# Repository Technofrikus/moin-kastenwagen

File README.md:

# Moinboards Kastenwagen Alu PCB

Kastenwagen Alu is based on the [Kastenwagen 1840 by NoPunin10did](https://github.com/nopunin10did/kastenwagen/tree/main). It is a 40% keyboard with a mini-numpad and dedicated arrows. The main alpha block is 13.75u long, allowing for more dedicated punctuation keys (or non-English letters) to be paired with common Minivan-like mod keys.

- Keyboard Maintainer: [Technofrikus](https://github.com/Technofrikus) from [Moinboards](https://moinboards.de)
- Onboard STM32 MCU
- Based on the original PCB by NoPunin10did, but basically completely new and NOT compatible with the previous (printed) Kastenwagen case or PCB.
- Works with VIAL

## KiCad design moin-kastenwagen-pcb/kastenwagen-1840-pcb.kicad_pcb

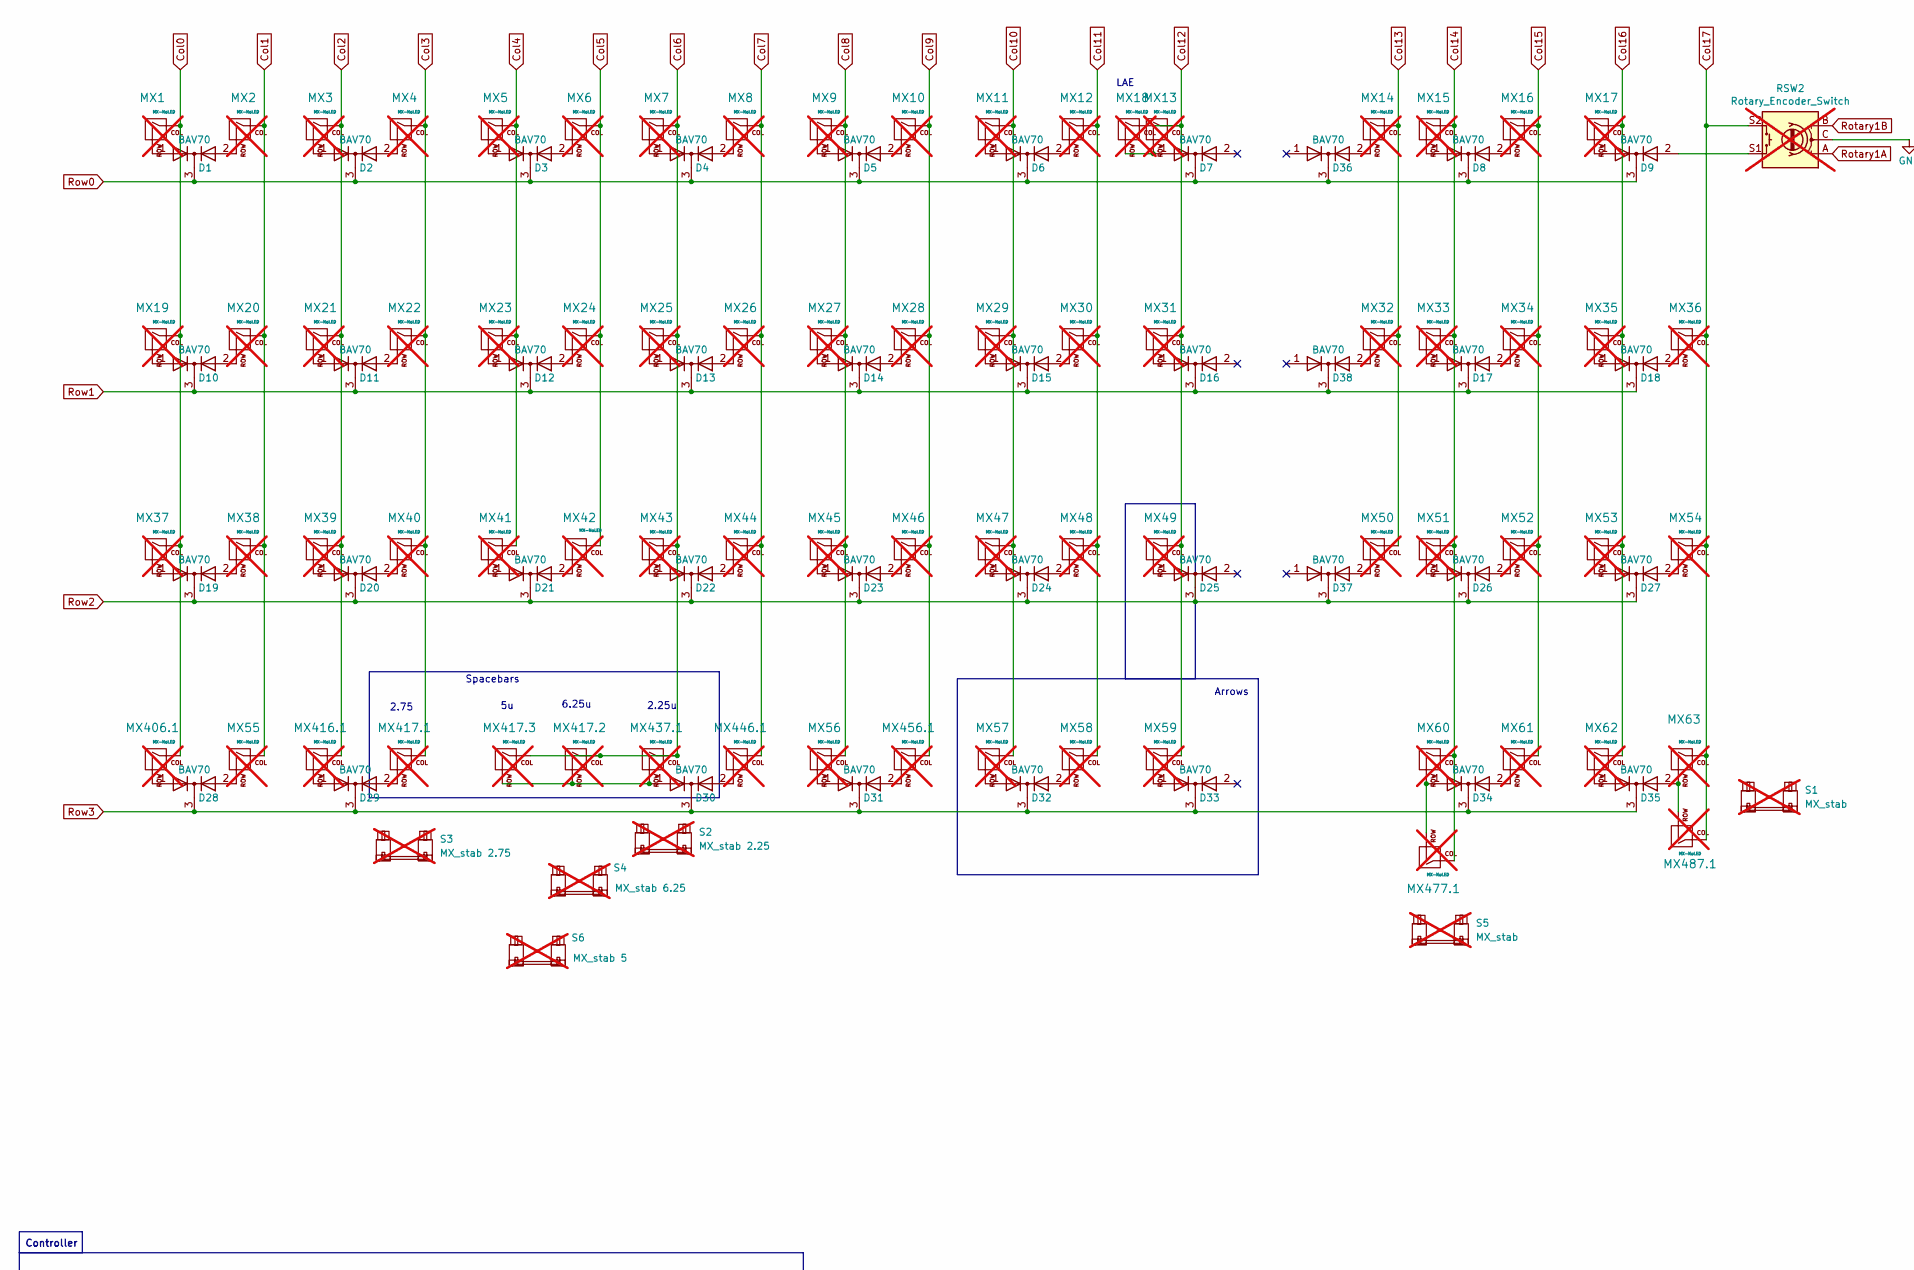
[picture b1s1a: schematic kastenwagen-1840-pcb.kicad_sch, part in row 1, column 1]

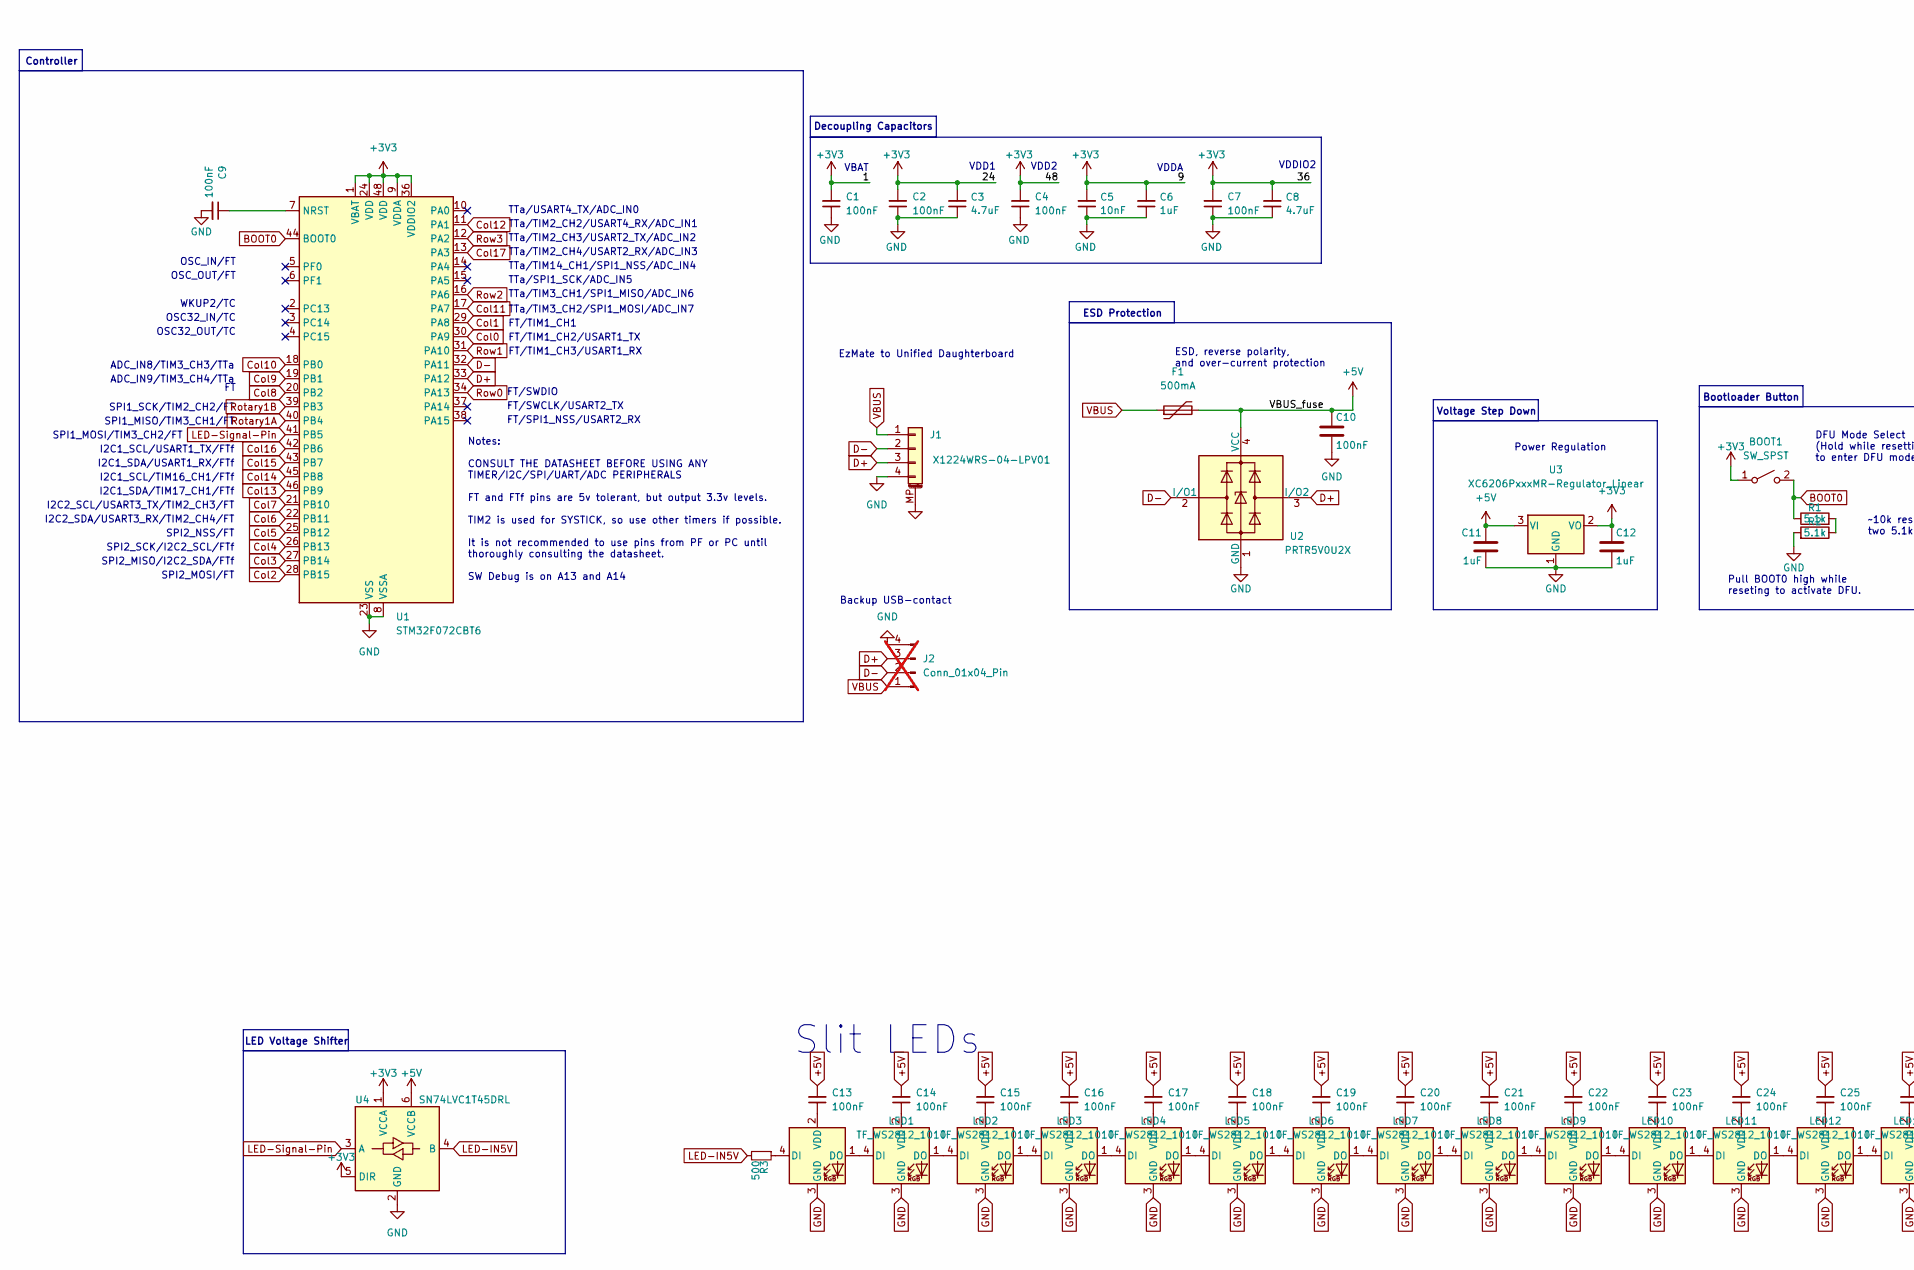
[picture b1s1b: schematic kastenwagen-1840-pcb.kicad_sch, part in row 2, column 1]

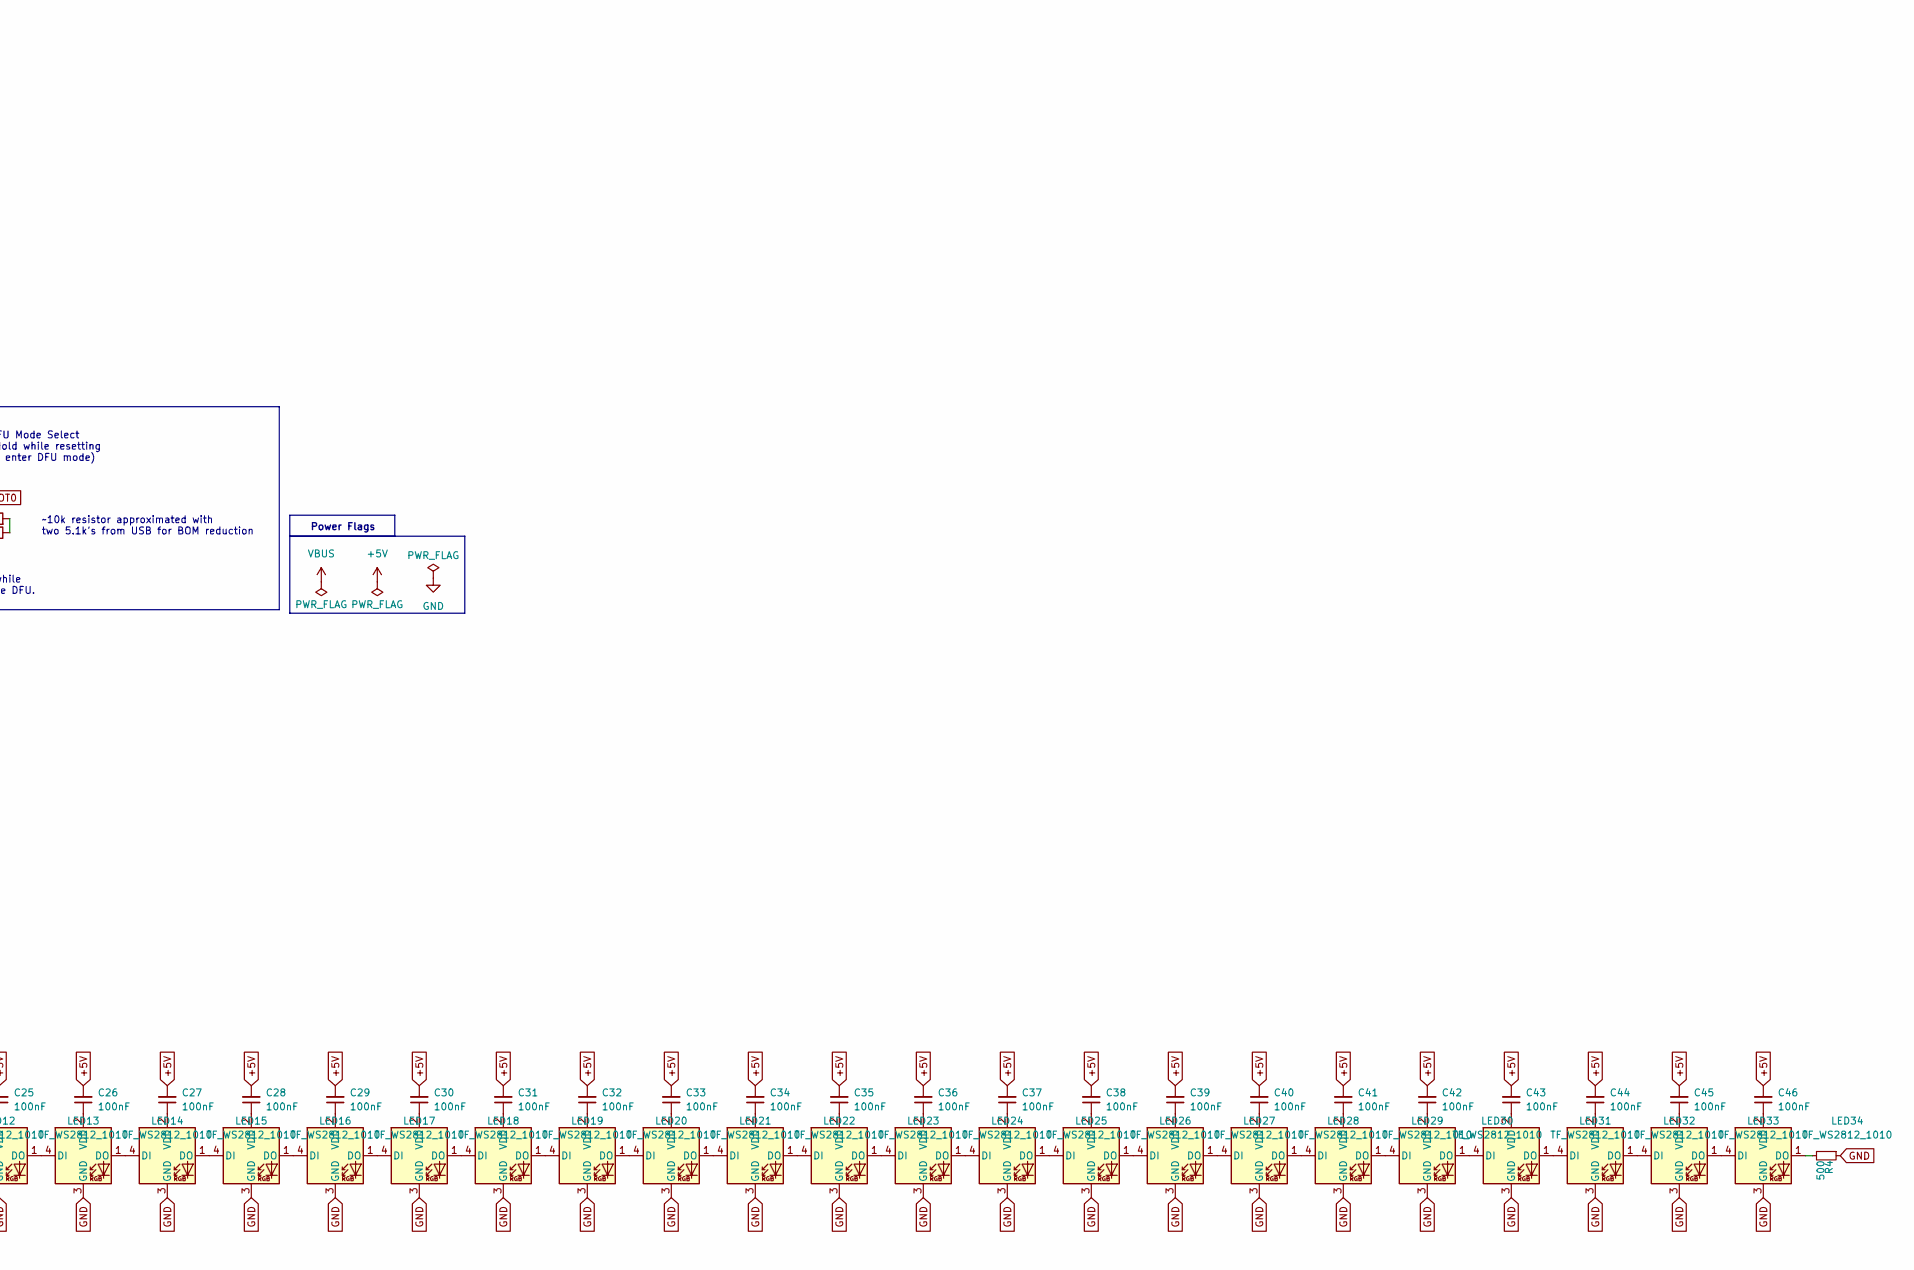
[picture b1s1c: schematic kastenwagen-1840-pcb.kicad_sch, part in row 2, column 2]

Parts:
BOOT1: SW_SPST; SW_SPST_TL3342; Mfr Part TS-1187A-B-A-B; LCSC C318884
C1, C2, C4, C7, C9, C10, C13, C14, C15, C16, C17, C18, C19, C20, C21, C22, C23, C24, C25, C26, C27, C28, C29, C30, C31, C32, C33, C34, C35, C36, C37, C38, C39, C40, C41, C42, C43, C44, C45, C46: 100nF; C_0402_1005Metric; MPN CL05B104KB54PNC; LCSC C307331
C3, C8: 4.7uF; C_0402_1005Metric; MPN CL05A475MP5NRNC; LCSC C23733
C5: 10nF; C_0402_1005Metric; MPN CL05B103KB5NNNC; LCSC C15195
C6, C11, C12: 1uF; C_0402_1005Metric; MPN CL05A105KA5NQNC; LCSC C52923
D1, D2, D3, D4, D5, D6, D7, D8, D9, D10, D11, D12, D13, D14, D15, D16, D17, D18, D19, D20, D21, D22, D23, D24, D25, D26, D27, D28, D29, D30, D31, D32, D33, D34, D35, D36, D37, D38: BAV70; SOT-23; MPN BAV70; LCSC C68978
F1: 500mA; Fuse_1206_3216Metric; MPN ASMD1206-150; LCSC C135341
J1: X1224WRS-04-LPV01; Molex_Pico-EZmate_78171-0004_1x04-1MP_P1.20mm_Vertical; Manufacturer Part Number 781710004; LCSC C588524
J2: Conn_01x04_Pin; PinSocket_1x04_P2.54mm_Vertical; not fitted
LED1, LED2, LED3, LED4, LED5, LED6, LED7, LED8, LED9, LED10, LED11, LED12, LED13, LED14, LED15, LED16, LED17, LED18, LED19, LED20, LED21, LED22, LED23, LED24, LED25, LED26, LED27, LED28, LED29, LED30, LED31, LED32, LED33, LED34: TF_WS2812_1010; LED_WS2812B_1010_Xinlight; MPN XL-1010RGBC-2812B; LCSC C5349953
MX1, MX2, MX3, MX4, MX5, MX6, MX7, MX8, MX9, MX10, MX11, MX12, MX14, MX15, MX16, MX17, MX20, MX21, MX22, MX23, MX24, MX25, MX26, MX27, MX28, MX29, MX30, MX32, MX33, MX34, MX35, MX36, MX38, MX39, MX40, MX41, MX42, MX43, MX44, MX45, MX46, MX47, MX49, MX50, MX51, MX52, MX53, MX54, MX55, MX56, MX57, MX58, MX59, MX60, MX61, MX62, MX63, MX417.1, MX417.2, MX417.3, MX437.1, MX477.1, MX487.1: MX-NoLED; SW_MX_HS_CPG151101S11_1u+3d; not fitted
MX13, MX37: MX-NoLED; SW_MX_HS_CPG151101S11_1.75u+3d; not fitted
MX18: MX-NoLED; SW_MX_1u; not fitted
MX19, MX48, MX406.1, MX416.1, MX446.1, MX456.1: MX-NoLED; SW_MX_HS_CPG151101S11_1.25u+3d; not fitted
MX31: MX-NoLED; SW_MX_HS_CPG151101S11_1.5u_+3d; not fitted
R1, R2: 5.1k; R_0402_1005Metric; MPN FRC0402J512 TS; LCSC C2906948
R3, R4: 500; R_0402_1005Metric; MPN RT0402FRE07500RL; LCSC C6460545
RSW2: Rotary_Encoder_Switch; ROT_Alps_EC11E-Switch; not fitted
S1, S5: MX_stab; STAB_MX_P_2u; not fitted
S2: MX_stab 2.25; STAB_MX_P_2.25u_sizelabel; not fitted
S3: MX_stab 2.75; STAB_MX_P_2.75u_sizelabel; not fitted
S4: MX_stab 6.25; STAB_MX_P_6.25u_sizelabel; not fitted
S6: MX_stab 5; MXOnly-5U-NoSwitch; not fitted
U1: STM32F072CBT6; LQFP-48_7x7mm_P0.5mm; MPN STM32F072CBT6; LCSC C81720
U2: PRTR5V0U2X; SOT-143; MPN PRTR5V0U2X; LCSC C2827688
U3: XC6206PxxxMR-Regulator_Linear; SOT-23; MPN XC6206P332MR-G; LCSC C5446
U4: SN74LVC1T45DRL; SOT-563; MPN SN74LVC1T45DRLR; LCSC C352970

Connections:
+3V3: BOOT1.1 (A), C1.2, C2.2, C3.2, C4.2, C5.2, C6.2, C7.2, C8.2, C12.1, U1.1 (VBAT), U1.9 (VDDA), U1.24 (VDD), U1.36 (VDDIO2), U1.48 (VDD), U3.2 (VO), U4.1 (VCCA), U4.5 (DIR)
+5V: C10.1, C11.1, C13.2, C14.2, C15.2, C16.2, C17.2, C18.2, C19.2, C20.2, C21.2, C22.2, C23.2, C24.2, C25.2, C26.2, C27.2, C28.2, C29.2, C30.2, C31.2, C32.2, C33.2, C34.2, C35.2, C36.2, C37.2, C38.2, C39.2, C40.2, C41.2, C42.2, C43.2, C44.2, C45.2, C46.2, F1.2, U2.4 (VCC), U3.3 (VI), U4.6 (VCCB)
BOOT0: BOOT1.2 (B), R1.1, U1.44 (BOOT0)
Col0: MX1.1 (COL), MX19.1 (COL), MX37.1 (COL), MX406.1.1 (COL), U1.30 (PA9)
Col1: MX2.1 (COL), MX20.1 (COL), MX38.1 (COL), MX55.1 (COL), U1.29 (PA8)
Col2: MX3.1 (COL), MX21.1 (COL), MX39.1 (COL), MX416.1.1 (COL), U1.28 (PB15)
Col3: MX4.1 (COL), MX22.1 (COL), MX40.1 (COL), MX417.1.1 (COL), U1.27 (PB14)
Col4: MX5.1 (COL), MX23.1 (COL), MX41.1 (COL), U1.26 (PB13)
Col5: MX6.1 (COL), MX24.1 (COL), MX42.1 (COL), U1.25 (PB12)
Col6: MX7.1 (COL), MX25.1 (COL), MX43.1 (COL), MX417.2.1 (COL), MX417.3.1 (COL), MX437.1.1 (COL), U1.22 (PB11)
Col7: MX8.1 (COL), MX26.1 (COL), MX44.1 (COL), MX446.1.1 (COL), U1.21 (PB10)
Col8: MX9.1 (COL), MX27.1 (COL), MX45.1 (COL), MX56.1 (COL), U1.20 (PB2)
Col9: MX10.1 (COL), MX28.1 (COL), MX46.1 (COL), MX456.1.1 (COL), U1.19 (PB1)
Col10: MX11.1 (COL), MX29.1 (COL), MX47.1 (COL), MX57.1 (COL), U1.18 (PB0)
Col11: MX12.1 (COL), MX30.1 (COL), MX48.1 (COL), MX58.1 (COL), U1.17 (PA7)
Col12: MX13.1 (COL), MX18.1 (COL), MX31.1 (COL), MX49.1 (COL), MX59.1 (COL), U1.11 (PA1)
Col13: MX14.1 (COL), MX32.1 (COL), MX50.1 (COL), U1.46 (PB9)
Col14: MX15.1 (COL), MX33.1 (COL), MX51.1 (COL), MX60.1 (COL), MX477.1.1 (COL), U1.45 (PB8)
Col15: MX16.1 (COL), MX34.1 (COL), MX52.1 (COL), MX61.1 (COL), U1.43 (PB7)
Col16: MX17.1 (COL), MX35.1 (COL), MX53.1 (COL), MX62.1 (COL), U1.42 (PB6)
Col17: MX36.1 (COL), MX54.1 (COL), MX63.1 (COL), MX487.1.1 (COL), RSW2.S2, U1.13 (PA3)
D+: J1.3, J2.3, U1.33 (PA12), U2.3 (I/O2)
D-: J1.2, J2.2, U1.32 (PA11), U2.2 (I/O1)
GND: C1.1, C2.1, C3.1, C4.1, C5.1, C6.1, C7.1, C8.1, C9.2, C10.2, C11.2, C12.2, J1.4, J1.MP (MountPin), J2.4, LED1.3 (GND), LED2.3 (GND), LED3.3 (GND), LED4.3 (GND), LED5.3 (GND), LED6.3 (GND), LED7.3 (GND), LED8.3 (GND), LED9.3 (GND), LED10.3 (GND), LED11.3 (GND), LED12.3 (GND), LED13.3 (GND), LED14.3 (GND), LED15.3 (GND), LED16.3 (GND), LED17.3 (GND), LED18.3 (GND), LED19.3 (GND), LED20.3 (GND), LED21.3 (GND), LED22.3 (GND), LED23.3 (GND), LED24.3 (GND), LED25.3 (GND), LED26.3 (GND), LED27.3 (GND), LED28.3 (GND), LED29.3 (GND), LED30.3 (GND), LED31.3 (GND), LED32.3 (GND), LED33.3 (GND), LED34.3 (GND), R2.2, R4.1, RSW2.C, U1.8 (VSSA), U1.23 (VSS), U1.35 (VSS), U1.47 (VSS), U2.1 (GND), U3.1 (GND), U4.2 (GND)
LED-IN5V: R3.2, U4.4 (B)
LED-Signal-Pin: U1.41 (PB5), U4.3 (A)
unnamed: D9.2 (A), RSW2.S1
unnamed: LED1.4 (DI), R3.1
unnamed: LED1.1 (DO), LED2.4 (DI)
unnamed: C13.1, LED1.2 (VDD)
unnamed: LED2.1 (DO), LED3.4 (DI)
unnamed: C14.1, LED2.2 (VDD)
unnamed: LED3.1 (DO), LED4.4 (DI)
unnamed: C15.1, LED3.2 (VDD)
unnamed: LED4.1 (DO), LED5.4 (DI)
unnamed: C16.1, LED4.2 (VDD)
unnamed: LED5.1 (DO), LED6.4 (DI)
unnamed: C17.1, LED5.2 (VDD)
unnamed: LED6.1 (DO), LED7.4 (DI)
unnamed: C18.1, LED6.2 (VDD)
unnamed: LED7.1 (DO), LED8.4 (DI)
unnamed: C19.1, LED7.2 (VDD)
unnamed: LED8.1 (DO), LED9.4 (DI)
unnamed: C20.1, LED8.2 (VDD)
unnamed: C21.1, LED9.2 (VDD)
unnamed: LED9.1 (DO), LED10.4 (DI)
unnamed: LED10.1 (DO), LED11.4 (DI)
unnamed: C22.1, LED10.2 (VDD)
unnamed: LED11.1 (DO), LED12.4 (DI)
unnamed: C23.1, LED11.2 (VDD)
unnamed: LED12.1 (DO), LED13.4 (DI)
unnamed: C24.1, LED12.2 (VDD)
unnamed: LED13.1 (DO), LED14.4 (DI)
unnamed: C25.1, LED13.2 (VDD)
unnamed: LED14.1 (DO), LED15.4 (DI)
unnamed: C26.1, LED14.2 (VDD)
unnamed: LED15.1 (DO), LED16.4 (DI)
unnamed: C27.1, LED15.2 (VDD)
unnamed: LED16.1 (DO), LED17.4 (DI)
unnamed: C28.1, LED16.2 (VDD)
unnamed: LED17.1 (DO), LED18.4 (DI)
unnamed: C29.1, LED17.2 (VDD)
unnamed: LED18.1 (DO), LED19.4 (DI)
unnamed: C30.1, LED18.2 (VDD)
unnamed: LED19.1 (DO), LED20.4 (DI)
unnamed: C31.1, LED19.2 (VDD)
unnamed: LED20.1 (DO), LED21.4 (DI)
unnamed: C32.1, LED20.2 (VDD)
unnamed: LED21.1 (DO), LED22.4 (DI)
unnamed: C33.1, LED21.2 (VDD)
unnamed: LED22.1 (DO), LED23.4 (DI)
unnamed: C34.1, LED22.2 (VDD)
unnamed: LED23.1 (DO), LED24.4 (DI)
unnamed: C35.1, LED23.2 (VDD)
unnamed: LED24.1 (DO), LED25.4 (DI)
unnamed: C36.1, LED24.2 (VDD)
unnamed: LED25.1 (DO), LED26.4 (DI)
unnamed: C37.1, LED25.2 (VDD)
unnamed: LED26.1 (DO), LED27.4 (DI)
unnamed: C38.1, LED26.2 (VDD)
unnamed: LED27.1 (DO), LED28.4 (DI)
unnamed: C39.1, LED27.2 (VDD)
unnamed: LED28.1 (DO), LED29.4 (DI)
unnamed: C40.1, LED28.2 (VDD)
unnamed: LED29.1 (DO), LED30.4 (DI)
unnamed: C41.1, LED29.2 (VDD)
unnamed: LED30.1 (DO), LED31.4 (DI)
unnamed: C42.1, LED30.2 (VDD)
unnamed: LED31.1 (DO), LED32.4 (DI)
unnamed: C43.1, LED31.2 (VDD)
unnamed: LED32.1 (DO), LED33.4 (DI)
unnamed: C44.1, LED32.2 (VDD)
unnamed: LED33.1 (DO), LED34.4 (DI)
unnamed: C45.1, LED33.2 (VDD)
unnamed: LED34.1 (DO), R4.2
unnamed: C46.1, LED34.2 (VDD)
unnamed: D1.1 (A), MX1.2 (ROW)
unnamed: D1.2 (A), MX2.2 (ROW)
unnamed: D2.1 (A), MX3.2 (ROW)
unnamed: D2.2 (A), MX4.2 (ROW)
unnamed: D3.1 (A), MX5.2 (ROW)
unnamed: D3.2 (A), MX6.2 (ROW)
unnamed: D4.1 (A), MX7.2 (ROW)
unnamed: D4.2 (A), MX8.2 (ROW)
unnamed: D5.1 (A), MX9.2 (ROW)
unnamed: D5.2 (A), MX10.2 (ROW)
unnamed: D6.1 (A), MX11.2 (ROW)
unnamed: D6.2 (A), MX12.2 (ROW)
unnamed: D7.1 (A), MX13.2 (ROW), MX18.2 (ROW)
unnamed: D36.2 (A), MX14.2 (ROW)
unnamed: D8.1 (A), MX15.2 (ROW)
unnamed: D8.2 (A), MX16.2 (ROW)
unnamed: D9.1 (A), MX17.2 (ROW)
unnamed: D10.1 (A), MX19.2 (ROW)
unnamed: D10.2 (A), MX20.2 (ROW)
unnamed: D11.1 (A), MX21.2 (ROW)
unnamed: D11.2 (A), MX22.2 (ROW)
unnamed: D12.1 (A), MX23.2 (ROW)
unnamed: D12.2 (A), MX24.2 (ROW)
unnamed: D13.1 (A), MX25.2 (ROW)
unnamed: D13.2 (A), MX26.2 (ROW)
unnamed: D14.1 (A), MX27.2 (ROW)
unnamed: D14.2 (A), MX28.2 (ROW)
unnamed: D15.1 (A), MX29.2 (ROW)
unnamed: D15.2 (A), MX30.2 (ROW)
unnamed: D16.1 (A), MX31.2 (ROW)
unnamed: D38.2 (A), MX32.2 (ROW)
unnamed: D17.1 (A), MX33.2 (ROW)
unnamed: D17.2 (A), MX34.2 (ROW)
unnamed: D18.1 (A), MX35.2 (ROW)
unnamed: D18.2 (A), MX36.2 (ROW)
unnamed: D19.1 (A), MX37.2 (ROW)
unnamed: D19.2 (A), MX38.2 (ROW)
unnamed: D20.1 (A), MX39.2 (ROW)
unnamed: D20.2 (A), MX40.2 (ROW)
unnamed: D21.1 (A), MX41.2 (ROW)
unnamed: D21.2 (A), MX42.2 (ROW)
unnamed: D22.1 (A), MX43.2 (ROW)
unnamed: D22.2 (A), MX44.2 (ROW)
unnamed: D23.1 (A), MX45.2 (ROW)
unnamed: D23.2 (A), MX46.2 (ROW)
unnamed: D24.1 (A), MX47.2 (ROW)
unnamed: D24.2 (A), MX48.2 (ROW)
unnamed: D25.1 (A), MX49.2 (ROW)
unnamed: D37.2 (A), MX50.2 (ROW)
unnamed: D26.1 (A), MX51.2 (ROW)
unnamed: D26.2 (A), MX52.2 (ROW)
unnamed: D27.1 (A), MX53.2 (ROW)
unnamed: D27.2 (A), MX54.2 (ROW)
unnamed: D28.2 (A), MX55.2 (ROW)
unnamed: D31.1 (A), MX56.2 (ROW)
unnamed: D32.1 (A), MX57.2 (ROW)
unnamed: D32.2 (A), MX58.2 (ROW)
unnamed: D33.1 (A), MX59.2 (ROW)
unnamed: D34.2 (A), MX61.2 (ROW)
unnamed: D35.1 (A), MX62.2 (ROW)
unnamed: D28.1 (A), MX406.1.2 (ROW)
unnamed: D29.1 (A), MX416.1.2 (ROW)
unnamed: D29.2 (A), MX417.1.2 (ROW)
unnamed: D30.1 (A), MX417.2.2 (ROW), MX417.3.2 (ROW), MX437.1.2 (ROW)
unnamed: D30.2 (A), MX446.1.2 (ROW)
unnamed: D31.2 (A), MX456.1.2 (ROW)
unnamed: D34.1 (A), MX60.2 (ROW), MX477.1.2 (ROW)
unnamed: D35.2 (A), MX63.2 (ROW), MX487.1.2 (ROW)
unnamed: R1.2, R2.1
unnamed: C9.1, U1.7 (NRST)
Rotary1A: RSW2.A, U1.40 (PB4)
Rotary1B: RSW2.B, U1.39 (PB3)
Row0: D1.3 (K), D2.3 (K), D3.3 (K), D4.3 (K), D5.3 (K), D6.3 (K), D7.3 (K), D8.3 (K), D9.3 (K), D36.3 (K), U1.34 (PA13)
Row1: D10.3 (K), D11.3 (K), D12.3 (K), D13.3 (K), D14.3 (K), D15.3 (K), D16.3 (K), D17.3 (K), D18.3 (K), D38.3 (K), U1.31 (PA10)
Row2: D19.3 (K), D20.3 (K), D21.3 (K), D22.3 (K), D23.3 (K), D24.3 (K), D25.3 (K), D26.3 (K), D27.3 (K), D37.3 (K), U1.16 (PA6)
Row3: D28.3 (K), D29.3 (K), D30.3 (K), D31.3 (K), D32.3 (K), D33.3 (K), D34.3 (K), D35.3 (K), U1.12 (PA2)
VBUS: F1.1, J1.1, J2.1

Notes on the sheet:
WKUP2/TC
FT/TIM1_CH3/USART1_RX
TTa/TIM3_CH2/SPI1_MOSI/ADC_IN7
6.25u
Pull BOOT0 high while reseting to activate DFU.
SPI2_SCK/I2C2_SCL/FTf
TTa/SPI1_SCK/ADC_IN5
TTa/TIM14_CH1/SPI1_NSS/ADC_IN4
FT/SPI1_NSS/USART2_RX
VDD2
TTa/TIM3_CH1/SPI1_MISO/ADC_IN6
Arrows
Controller
SPI2_MISO/I2C2_SDA/FTf
EzMate to Unified Daughterboard
VBAT
Decoupling Capacitors
Bootloader Button
I2C1_SCL/USART1_TX/FTf
LAE
ADC_IN8/TIM3_CH3/TTa
Spacebars
OSC_IN/FT
ADC_IN9/TIM3_CH4/TTa
OSC32_IN/TC
SPI1_MISO/TIM3_CH1/FT
OSC32_OUT/TC
LED Voltage Shifter
I2C1_SDA/TIM17_CH1/FTf
Power Flags
SPI2_NSS/FT
Backup USB-contact
~10k resistor approximated with two 5.1k's from USB for BOM reduction
TTa/TIM2_CH4/USART2_RX/ADC_IN3
OSC_OUT/FT
FT/SWDIO
ESD, reverse polarity, and over-current protection
I2C2_SCL/USART3_TX/TIM2_CH3/FT
SPI1_MOSI/TIM3_CH2/FT
Voltage Step Down

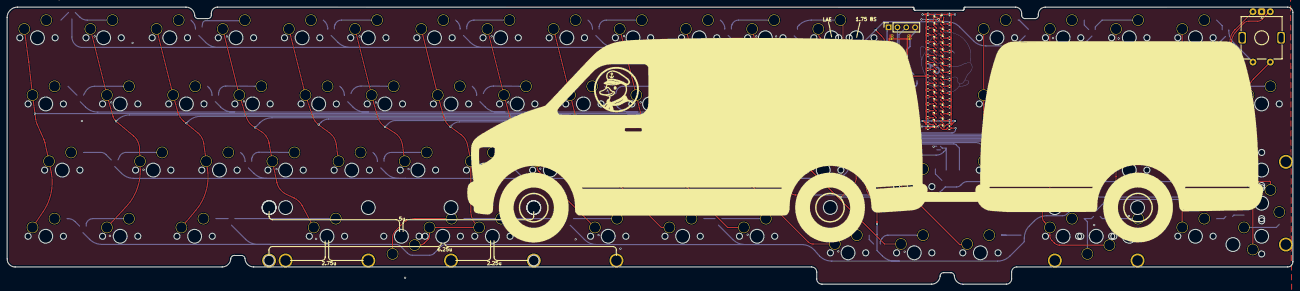
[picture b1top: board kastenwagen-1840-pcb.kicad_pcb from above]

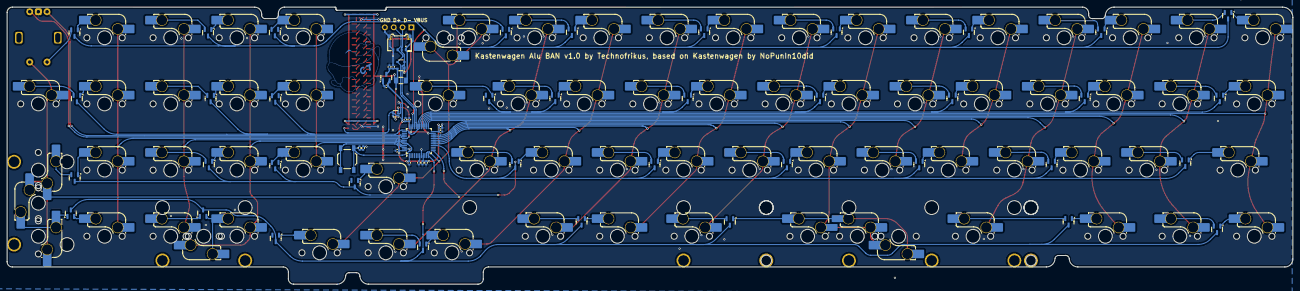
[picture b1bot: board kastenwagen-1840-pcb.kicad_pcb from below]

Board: 2 copper layers, 370.2 x 79.8 mm, 212 parts (132 on the bottom side), 173 nets.

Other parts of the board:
Ref**: Val**; Moinboards new logo
Ref**#2: Val**; Kastenwagen Logo - Silkscreen mirrored filled

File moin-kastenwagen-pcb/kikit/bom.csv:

"Reference","MPN","Qty","Original","Value","Purchase Link","DNP","LCSC","Manufacturer"
"BOOT1","TS-1187A-B-A-B","1","N","SW_SPST","https://www.lcsc.com/product-detail/C318884.html?s_z=n_C318884","","C318884","XKB Connection"
"C1,C2,C4,C7,C9,C10,C13,C14,C15,C16,C17,C18,C19,C20,C21,C22,C23,C24,C25,C26,C27,C28,C29,C30,C31,C32,C33,C34,C35,C36,C37,C38,C39,C40,C41,C42,C43,C44,C45,C46","CL05B104KB54PNC","40","N","100nF","https://www.lcsc.com/product-detail/C307331.html?s_z=n_C307331","","C307331","Samsung Electro-Mechanics"
"C3,C8","CL05A475MP5NRNC","2","N","4.7uF","https://www.lcsc.com/product-detail/C23733.html?s_z=n_C23733","","C23733","Samsung Electro-Mechanics"
"C5","CL05B103KB5NNNC","1","N","10nF","https://www.lcsc.com/product-detail/C15195.html?s_z=n_C15195","","C15195","Samsung Electro-Mechanics"
"C6,C11,C12","CL05A105KA5NQNC","3","N","1uF","https://www.lcsc.com/product-detail/C52923.html?s_z=n_C52923","","C52923","Samsung Electro-Mechanics"
"D1,D2,D3,D4,D5,D6,D7,D8,D9,D10,D11,D12,D13,D14,D15,D16,D17,D18,D19,D20,D21,D22,D23,D24,D25,D26,D27,D28,D29,D30,D31,D32,D33,D34,D35,D36,D37,D38","BAV70","38","N","BAV70","https://www.lcsc.com/product-detail/C68978.html?s_z=n_C68978","","C68978","JSCJ"
"F1","ASMD1206-150","1","N","500mA","https://www.lcsc.com/product-detail/C135341.html?s_z=n_C135341","","C135341","JDTfuse"
"J1","781710004","1","Y","X1224WRS-04-LPV01","https://www.lcsc.com/product-detail/C588524.html?s_z=n_C588524","","C588524","Molex"
"LED1,LED2,LED3,LED4,LED5,LED6,LED7,LED8,LED9,LED10,LED11,LED12,LED13,LED14,LED15,LED16,LED17,LED18,LED19,LED20,LED21,LED22,LED23,LED24,LED25,LED26,LED27,LED28,LED29,LED30,LED31,LED32,LED33,LED34","XL-1010RGBC-2812B","34","Y","TF_WS2812_1010","https://www.lcsc.com/product-detail/C5349953.html?s_z=n_C5349953","","C5349953","XINGLIGHT"
"R1,R2","FRC0402J512 TS","2","N","5.1k","https://www.lcsc.com/product-detail/C2906948.html","","C2906948","FOJAN"
"R3,R4","RT0402FRE07500RL","2","N","500","https://www.lcsc.com/product-detail/C6460545.html","","C6460545","YAGEO"
"U1","STM32F072CBT6","1","Y","STM32F072CBT6","https://www.lcsc.com/product-detail/C81720.html?s_z=n_STM32F072CBT6","","C81720","ST"
"U2","PRTR5V0U2X","1","N","PRTR5V0U2X","https://www.lcsc.com/product-detail/C2827688.html?s_z=n_C2827688","","C2827688","TECH PUBLIC"
"U3","XC6206P332MR-G","1","N","XC6206PxxxMR-Regulator_Linear","https://www.lcsc.com/product-detail/C5446.html?s_z=n_C5446","","C5446","TOREX"
"U4","SN74LVC1T45DRLR","1","N","SN74LVC1T45DRL","https://www.lcsc.com/product-detail/C352970.html?s_z=n_SN74L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","","C352970","TI"

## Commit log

2024-10-08 Untestested v1 finished. Ready for Protos.
2024-10-08 Finished Plate v1, Added correct Readme
2024-10-08 Updated gitignore to include production files
2024-10-08 effing DS_Store
2026-01-25 PCB und Plate bestellfertig
